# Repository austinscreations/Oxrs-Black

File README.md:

# Oxrs-Black
a custom rack controller that is based of the rack32 but includes some upgrades and major changes

With the latest update on 2024-08-09
- known part qty missing for the optoisolators - these are needed for KNX function. 

you can leave them off or preorder the part before PCBa from JLC
- https://jlcpcb.com/partdetail/avago_broadcom-ACPL_M61L500E/C44908

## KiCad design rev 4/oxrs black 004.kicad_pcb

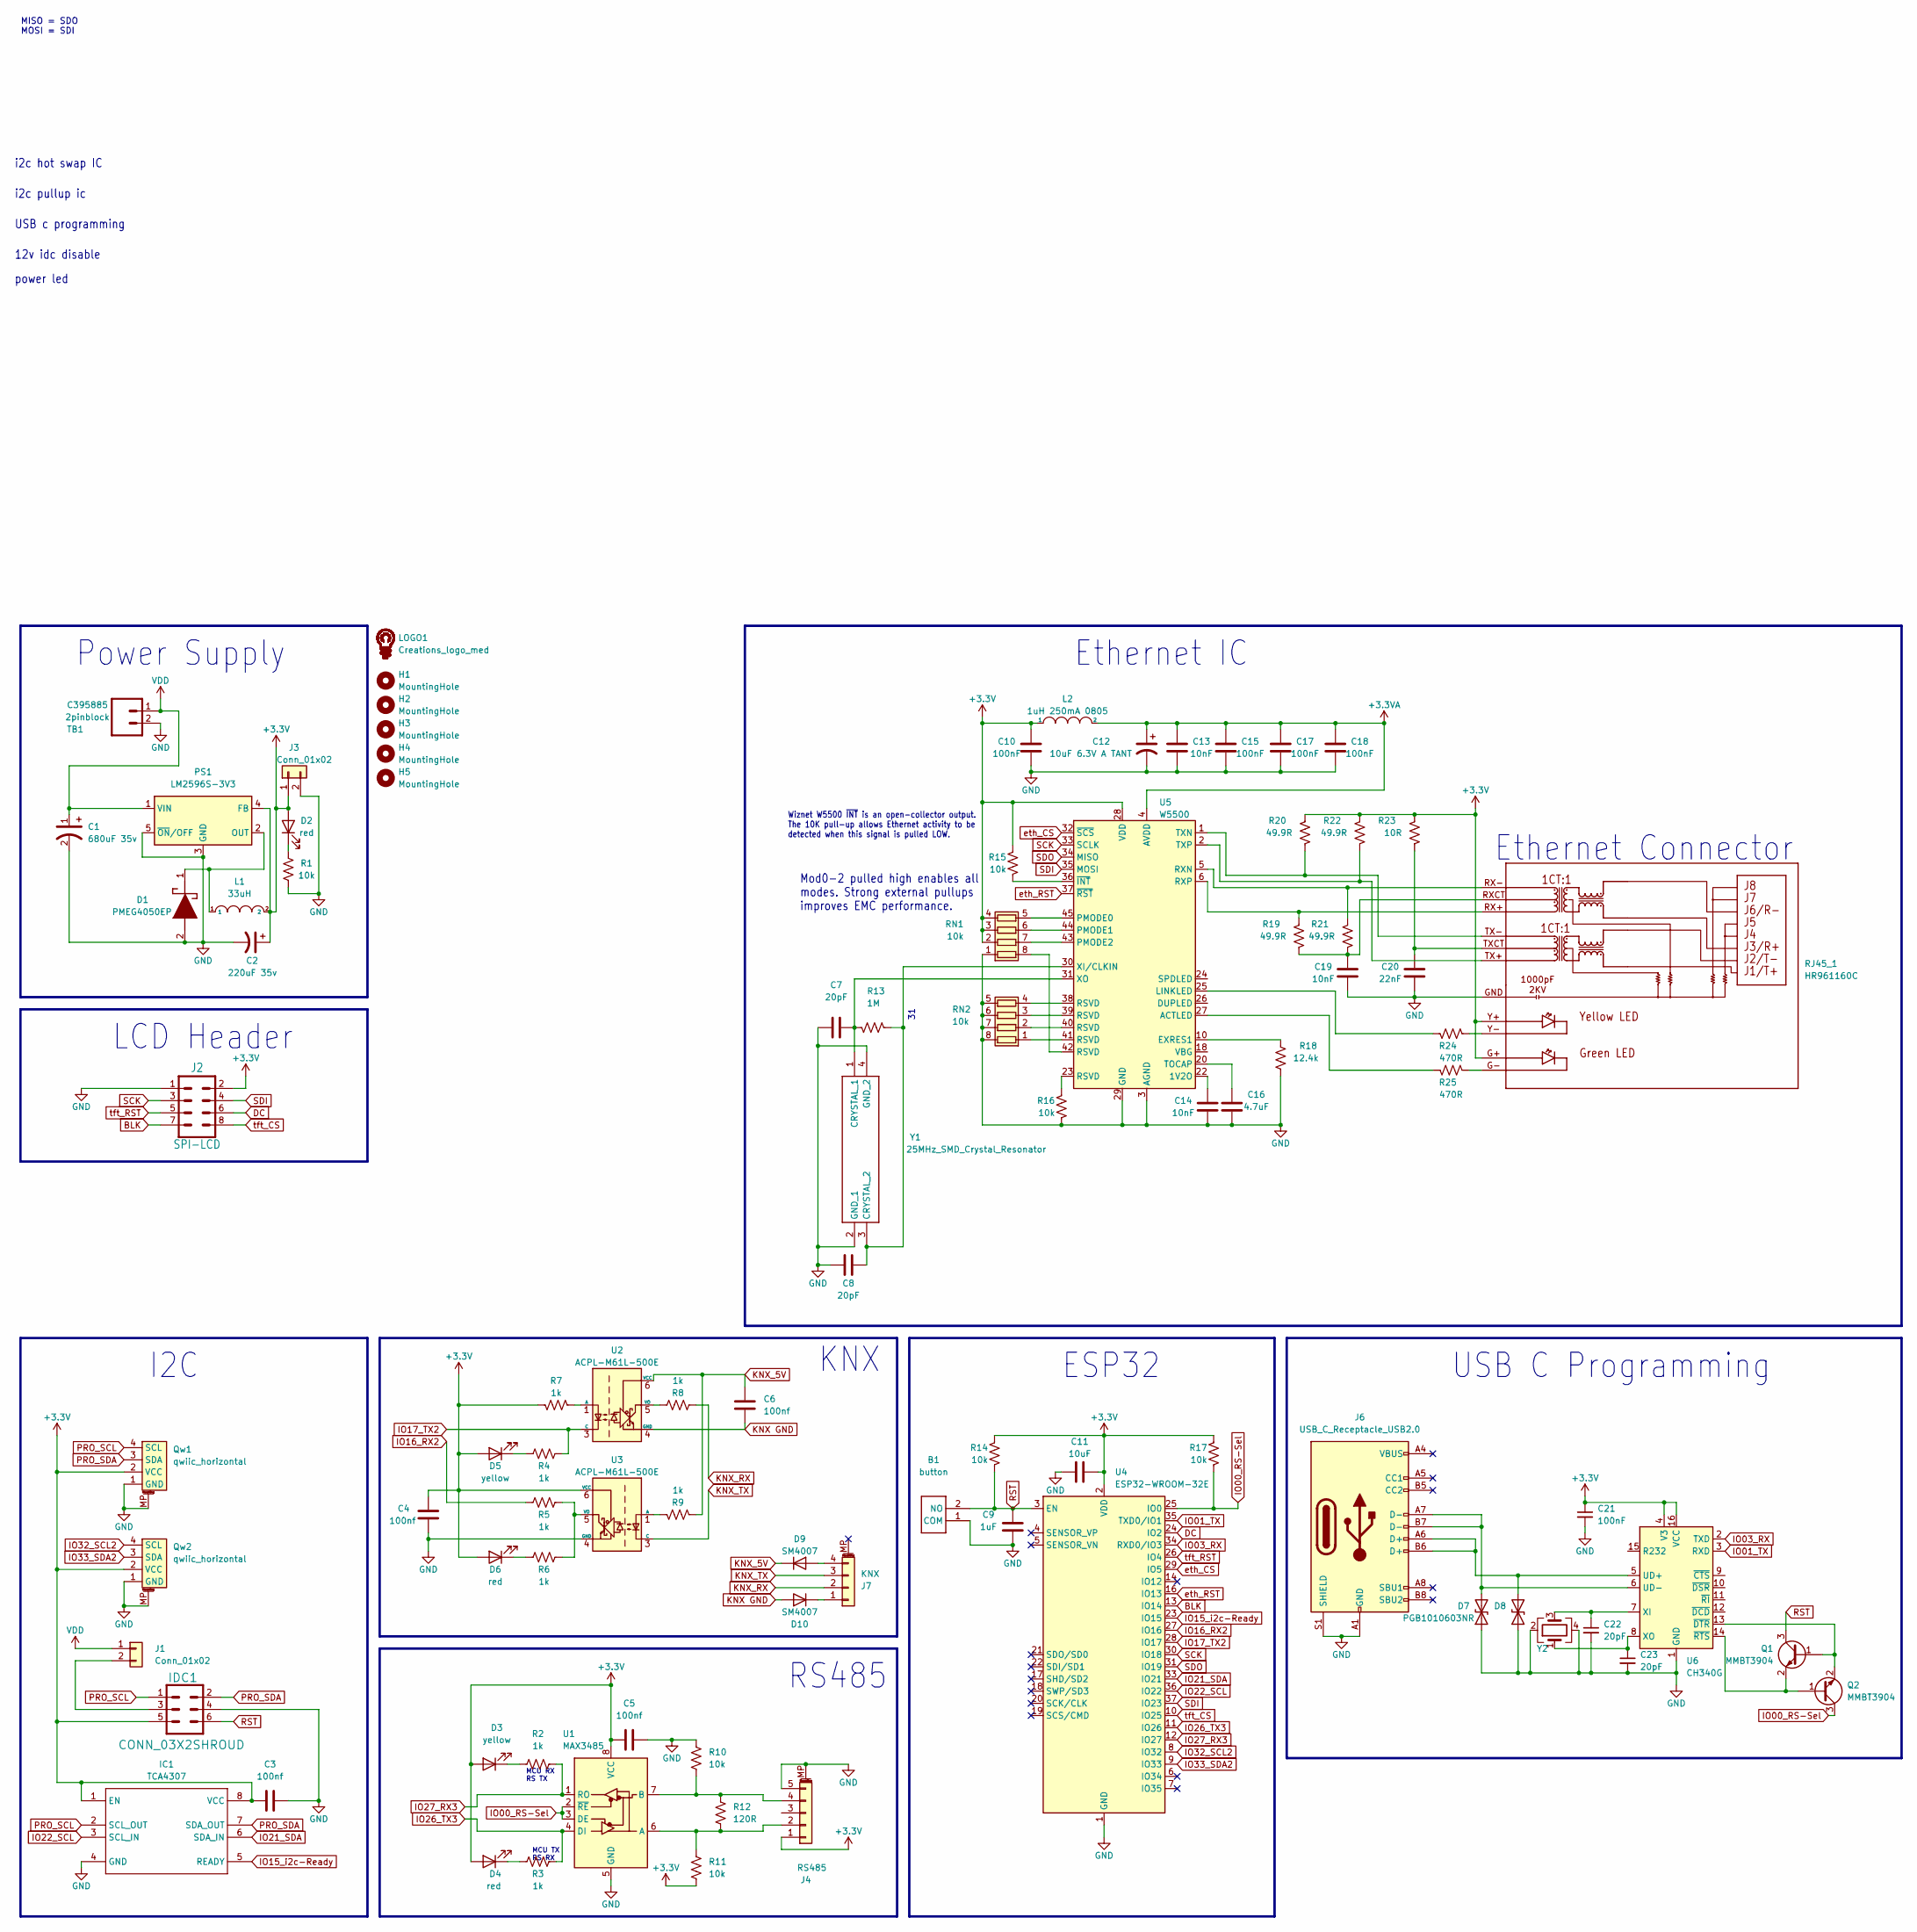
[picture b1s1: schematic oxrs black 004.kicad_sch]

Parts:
B1: button; LCSC C410373
C1: 680uF 35v; large capacitor 12.5d 13.5h; LCSC C98216
C2: 220uF 35v; CP_Elec_8x6.2; LCSC C5162357
C3, C4, C5, C6: 100nf; C_0603_1608Metric; LCSC C14663
C7, C8, C22, C23: 20pF; C_0603_1608Metric; LCSC C1648
C9: 1uF; C_0603_1608Metric; LCSC C15849
C10, C15, C17, C18, C21: 100nF; C_0603_1608Metric; LCSC C14663
C11: 10uF; C_0603_1608Metric; LCSC C19702
C12: 10uF 6.3V A TANT; CP_EIA-3216-18_Kemet-A; LCSC C127946
C13, C14, C19: 10nF; C_0603_1608Metric; LCSC C57112
C16: 4.7uF; C_0603_1608Metric; LCSC C19666
C20: 22nF; C_0603_1608Metric; LCSC C21122
D1: PMEG4050EP; PMEG3050EP; LCSC C96235
D2, D4, D6: red; LED_0603_1608Metric; LCSC C2286
D3, D5: yellow; LED_0603_1608Metric; LCSC C72038
D7, D8: PGB1010603NR; D_0603_1608Metric; LCSC C10677
D9, D10: SM4007; D_SOD-123F; LCSC C64898
H1, H2, H3, H4, H5: MountingHole; MountingHole_3.2mm_M3
IC1: TCA4307; VSSOP-8_3.0x3.0mm_P0.65mm; LCSC C880333
IDC1: CONN_03X2SHROUD; IDC-Header_2x03_P2.54mm_Vertical; LCSC C601936
J1, J3: Conn_01x02; PinHeader_1x02_P2.54mm_Vertical; LCSC C492401
J2: SPI-LCD; IDC-Header_2x04_P2.54mm_Vertical; LCSC C601937
J4: RS485; 5 pin jst 1.25 vertical; LCSC C225107
J6: USB_C_Receptacle_USB2.0; USB_C_Receptacle_HRO_TYPE-C-31-M-12; LCSC C2765186
J7: KNX; 4 pin jst 1.25 vertical; LCSC C225106
L1: 33uH; 12x12x8 inductor; LCSC C9400
L2: 1uH 250mA 0805; L_0805_2012Metric; LCSC C98325
LOGO1: Creations_logo_med; Creations logo med
PS1: LM2596S-3V3; LM2596S; LCSC C347420
Q1, Q2: MMBT3904; SOT-23; LCSC C20526
Qw1, Qw2: qwiic_horizontal; qwiic vertical; part # C145961; LCSC C145956
R1, R10, R11, R14, R15, R16, R17: 10k; R_0603_1608Metric; LCSC C25804
R2, R3, R4, R5, R6, R7, R8, R9: 1k; R_0603_1608Metric; LCSC C21190
R12: 120R; R_0603_1608Metric; LCSC C22787
R13: 1M; R_0603_1608Metric; LCSC C22935
R18: 12.4k; R_0603_1608Metric; LCSC C310267
R19, R20, R21, R22: 49.9R; R_0603_1608Metric; LCSC C23185
R23: 10R; R_0603_1608Metric; LCSC C22859
R24, R25: 470R; R_0603_1608Metric; LCSC C23179
RJ45_1: HR961160C; LCSC C55683
RN1, RN2: 10k; R_Array_Convex_4x0603; LCSC C29718
TB1: 2pinblock; LCSC C395885
U1: MAX3485; SOP-8_3.9x4.9mm_P1.27mm; part # C9943; LCSC C668204
U2, U3: ACPL-M61L-500E; SO-5_4.4x3.6mm_P1.27mm; LCSC C44908
U4: ESP32-WROOM-32E; ESP32-WROOM-32; LCSC C3013935
U5: W5500; LQFP-48_7x7mm_P0.5mm; LCSC C32843
U6: CH340G; SOIC-16_3.9x9.9mm_P1.27mm; LCSC C14267
Y1: 25MHz_SMD_Crystal_Resonator; LCSC C258949
Y2: Crystal_GND23; Crystal_SMD_3225-4Pin_3.2x2.5mm; LCSC C9002

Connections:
+3.3VA: C12.1, C13.2, C15.2, C17.2, C18.2, L2.2, U5.4 (AVDD), U5.8 (AVDD), U5.11 (AVDD), U5.15 (AVDD), U5.17 (AVDD), U5.21 (AVDD)
+3V3: C2.1, C3.2, C4.1, C5.2, C10.2, C11.2, C21.1, D2.2 (A), D3.2 (A), D4.2 (A), D5.2 (A), D6.2 (A), IC1.1 (EN), IC1.8 (VCC), IDC1.5, J2.2, J3.1, J4.1, L1.2, L2.1, PS1.4 (FB), Qw1.2 (VCC), Qw2.2 (VCC), R7.1, R11.1, R14.2, R15.2, R17.2, R20.2, R22.2, R23.2, RJ45_1.G+, RJ45_1.Y+, RN1.2 (R2.1), RN1.3 (R3.1), RN1.4 (R4.1), U1.8 (VCC), U3.6 (VCC), U4.2 (VDD), U5.28 (VDD), U6.4 (V3), U6.16 (VCC)
BLK: J2.7, U4.13 (IO14)
DC: J2.6, U4.24 (IO2)
GND: B1.1 (COM), C1.2, C2.2, C3.1, C4.2, C5.1, C7.1, C8.1, C9.1, C10.1, C11.1, C12.2, C13.1, C14.1, C15.1, C16.1, C17.1, C18.1, C19.1, C20.1, C21.2, C22.2, C23.2, D1.2 (A), D7.1 (A1), D8.1 (A1), IC1.4 (GND), IDC1.4, J2.1, J3.2, J4.5, J4.MP (MountPin), J6.A1 (GND), J6.A12 (GND), J6.B1 (GND), J6.B12 (GND), J6.S1 (SHIELD), PS1.3 (GND), PS1.5 (~ON/OFF), Qw1.1 (GND), Qw1.MP, Qw2.1 (GND), Qw2.MP, R1.2, R10.2, R16.1, R18.1, RJ45_1.GND (GNDF), RN1.1 (R1.1), RN2.5 (R4.2), RN2.6 (R3.2), RN2.7 (R2.2), RN2.8 (R1.2), TB1.2, U1.5 (GND), U3.4 (GND), U4.1 (GND), U4.15 (GND), U4.38 (GND), U4.39 (GND), U5.3 (AGND), U5.9 (AGND), U5.14 (AGND), U5.16 (AGND), U5.19 (AGND), U5.29 (GND), U5.48 (AGND), U6.1 (GND), Y1.2 (GND_1), Y1.4 (GND_2), Y2.2, Y2.4
IO00_RS-Sel: Q2.3 (C), R17.1, U1.2 (~RE), U1.3 (DE), U4.25 (IO0)
IO01_TX: U4.35 (TXD0/IO1), U6.3 (RXD)
IO03_RX: U4.34 (RXD0/IO3), U6.2 (TXD)
IO15_i2c-Ready: IC1.5 (READY), U4.23 (IO15)
IO16_RX2: R5.1, U4.27 (IO16)
IO17_TX2: R4.2, U2.3 (C), U4.28 (IO17)
IO21_SDA: IC1.6 (SDA_IN), U4.33 (IO21)
IO22_SCL: IC1.3 (SCL_IN), U4.36 (IO22)
IO26_TX3: R3.2, U1.4 (DI), U4.11 (IO26)
IO27_RX3: R2.2, U1.1 (RO), U4.12 (IO27)
IO32_SCL2: Qw2.4 (SCL), U4.8 (IO32)
IO33_SDA2: Qw2.3 (SDA), U4.9 (IO33)
KNX GND: C6.2, D10.2 (A), U2.4 (GND)
KNX_5V: C6.1, D9.1 (K), R9.2, U2.6 (VCC)
KNX_RX: J7.2, R8.1
KNX_TX: J7.3, U3.3 (C)
unnamed: C19.2, R19.1, R21.1, RJ45_1.RXCT
unnamed: C20.2, R23.1, RJ45_1.TXCT
unnamed: D1.1 (K), L1.1, PS1.2 (OUT)
unnamed: D2.1 (K), R1.1
unnamed: D3.1 (K), R2.1
unnamed: D4.1 (K), R3.1
unnamed: D5.1 (K), R4.1
unnamed: D6.1 (K), R6.1
unnamed: D7.2 (A2), J6.A7 (D-), J6.B7 (D-), U6.6 (UD-)
unnamed: D8.2 (A2), J6.A6 (D+), J6.B6 (D+), U6.5 (UD+)
unnamed: D9.2 (A), J7.4
unnamed: D10.1 (K), J7.1
unnamed: IDC1.3, J1.2
unnamed: J4.2, R11.2, R12.1, U1.6 (A)
unnamed: J4.4, R10.1, R12.2, U1.7 (B)
unnamed: Q1.1 (B), Q2.2 (E), U6.13 (~DTR)
unnamed: Q1.2 (E), Q2.1 (B), U6.14 (~RTS)
unnamed: R16.2, U5.23 (RSVD)
unnamed: R24.1, RJ45_1.Y-
unnamed: R25.1, RJ45_1.G-
unnamed: RN1.8 (R1.2), U5.42 (RSVD)
unnamed: RN1.7 (R2.2), U5.43 (PMODE2)
unnamed: RN1.6 (R3.2), U5.44 (PMODE1)
unnamed: RN1.5 (R4.2), U5.45 (PMODE0)
unnamed: RN2.1 (R1.1), U5.41 (RSVD)
unnamed: RN2.2 (R2.1), U5.40 (RSVD)
unnamed: RN2.3 (R3.1), U5.39 (RSVD)
unnamed: RN2.4 (R4.1), U5.38 (RSVD)
unnamed: R7.2, U2.1 (A)
unnamed: R8.2, U2.5 (VO)
unnamed: R9.1, U3.1 (A)
unnamed: R5.2, R6.2, U3.5 (VO)
unnamed: C14.2, U5.22 (1V2O)
unnamed: R25.2, U5.27 (ACTLED)
unnamed: R18.2, U5.10 (EXRES1)
unnamed: R24.2, U5.25 (LINKLED)
unnamed: R21.2, RJ45_1.RX-, U5.5 (RXN)
unnamed: R19.2, RJ45_1.RX+, U5.6 (RXP)
unnamed: C16.2, U5.20 (TOCAP)
unnamed: R20.1, RJ45_1.TX-, U5.1 (TXN)
unnamed: R22.1, RJ45_1.TX+, U5.2 (TXP)
unnamed: C8.2, R13.2, U5.30 (XI/CLKIN), Y1.3 (CRYSTAL_2)
unnamed: C7.2, R13.1, U5.31 (XO), Y1.1 (CRYSTAL_1)
unnamed: R15.1, U5.36 (~INT)
unnamed: C22.1, U6.7 (XI), Y2.3
unnamed: C23.1, U6.8 (XO), Y2.1
PRO_SCL: IC1.2 (SCL_OUT), IDC1.1, Qw1.4 (SCL)
PRO_SDA: IC1.7 (SDA_OUT), IDC1.2, Qw1.3 (SDA)
RST: B1.2 (NO), C9.2, IDC1.6, Q1.3 (C), R14.1, U4.3 (EN)
SCK: J2.3, U4.30 (IO18), U5.33 (SCLK)
SDI: J2.4, U4.37 (IO23), U5.35 (MOSI)
SDO: U4.31 (IO19), U5.34 (MISO)
VDD: C1.1, J1.1, PS1.1 (VIN), TB1.1
eth_CS: U4.29 (IO5), U5.32 (~SCS)
eth_RST: U4.16 (IO13), U5.37 (~RST)
tft_CS: J2.8, U4.10 (IO25)
tft_RST: J2.5, U4.26 (IO4)

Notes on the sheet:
I2C
Power Supply
power led
ESP32
Mod0-2 pulled high enables all modes. Strong external pullups improves EMC performance.
LCD Header
KNX
MISO = SDO MOSI = SDI
i2c hot swap IC
i2c pullup ic
Ethernet Connector
USB C Programming
MCU RX RS TX
Ethernet IC
12v idc disable
RS485
MCU TX RS RX
USB c programming
Wiznet W5500 ~{INT} is an open-collector output. The 10K pull-up allows Ethernet activity to be detected when this signal is pulled LOW.

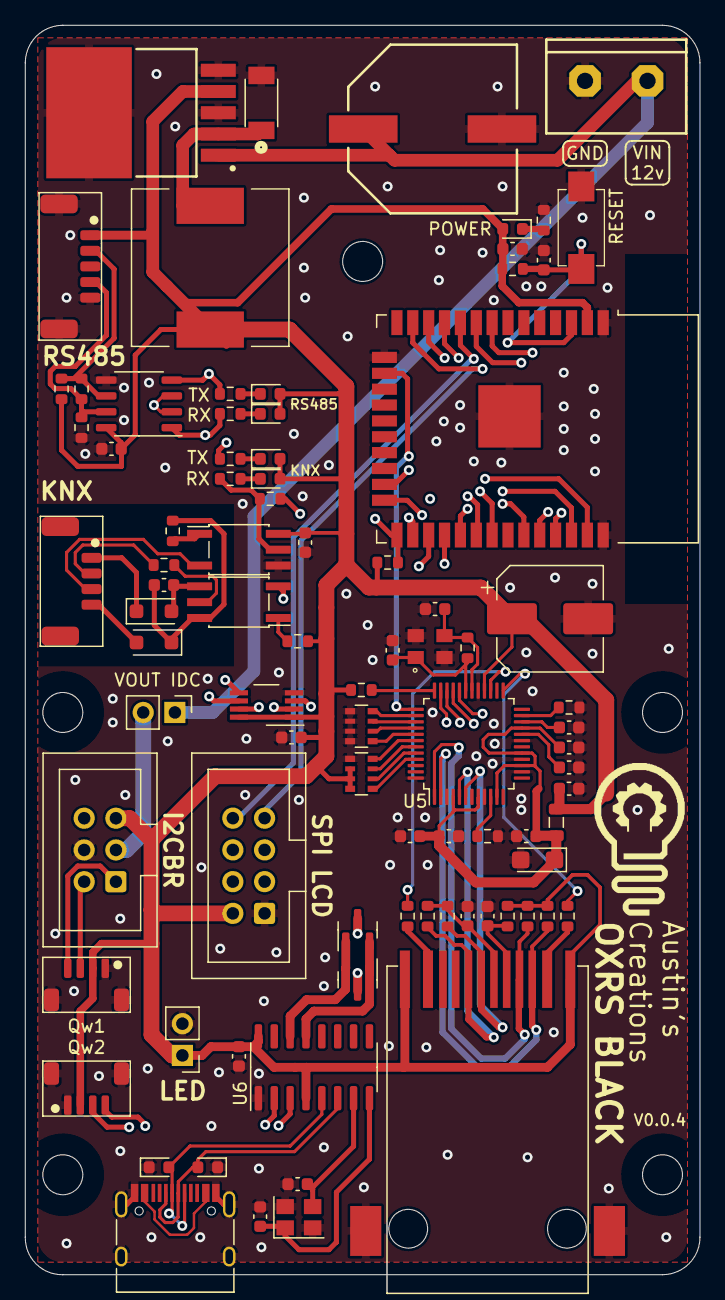
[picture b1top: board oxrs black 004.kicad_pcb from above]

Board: 4 copper layers, 54.0 x 100.0 mm, 92 parts (0 on the bottom side), 78 nets.

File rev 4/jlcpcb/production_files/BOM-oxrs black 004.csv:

Comment,Designator,Footprint,LCSC
PGB1010603NR,"D7,D8",D_0603_1608Metric,C10677
10uF 6.3V A TANT,C12,CP_EIA-3216-18_Kemet-A,C127946
CH340G,U6,SOIC-16_3.9x9.9mm_P1.27mm,C14267
qwiic_horizontal,"Qw1,Qw2",qwiic vertical,C145956
100nF,"C10,C15,C17,C18,C21,C3,C4,C5,C6",C_0603_1608Metric,C14663
1uF,C9,C_0603_1608Metric,C15849
20pF,"C22,C23,C7,C8",C_0603_1608Metric,C1648
4.7uF,C16,C_0603_1608Metric,C19666
10uF,C11,C_0603_1608Metric,C19702
MMBT3904,"Q1,Q2",SOT-23,C20526
22nF,C20,C_0603_1608Metric,C21122
1k,"R2,R3,R4,R5,R6,R7,R8,R9",R_0603_1608Metric,C21190
KNX,J7,4 pin jst 1.25 vertical,C225106
RS485,J4,5 pin jst 1.25 vertical,C225107
120R,R12,R_0603_1608Metric,C22787
10R,R23,R_0603_1608Metric,C22859
red,"D2,D4,D6",LED_0603_1608Metric,C2286
1M,R13,R_0603_1608Metric,C22935
470R,"R24,R25",R_0603_1608Metric,C23179
49.9R,"R19,R20,R21,R22",R_0603_1608Metric,C23185
10k,"R1,R10,R11,R14,R15,R16,R17",R_0603_1608Metric,C25804
25MHz_SMD_Crystal_Resonator,Y1,25MHz_SMD_Crystal_Resonator,C258949
USB_C_Receptacle_USB2.0,J6,USB_C_Receptacle_HRO_TYPE-C-31-M-12,C2765186
10k,"RN1,RN2",R_Array_Convex_4x0603,C29718
ESP32-WROOM-32E,U4,ESP32-WROOM-32,C3013935
12.4k,R18,R_0603_1608Metric,C310267
W5500,U5,LQFP-48_7x7mm_P0.5mm,C32843
LM2596S-3V3,PS1,LM2596S,C347420
2pinblock,TB1,2pinblock,C395885
button,B1,button,C410373
ACPL-M61L-500E,"U2,U3",SO-5_4.4x3.6mm_P1.27mm,C44908
Conn_01x02,"J1,J3",PinHeader_1x02_P2.54mm_Vertical,C492401
220uF 35v,C2,CP_Elec_8x6.2,C5162357
HR961160C,RJ45_1,HR961160C,C55683
10nF,"C13,C14,C19",C_0603_1608Metric,C57112
CONN_03X2SHROUD,IDC1,IDC-Header_2x03_P2.54mm_Vertical,C601936
SPI-LCD,J2,IDC-Header_2x04_P2.54mm_Vertical,C601937
SM4007,"D10,D9",D_SOD-123F,C64898
MAX3485,U1,SOP-8_3.9x4.9mm_P1.27mm,C668204
yellow,"D3,D5",LED_0603_1608Metric,C72038
TCA4307,IC1,VSSOP-8_3.0x3.0mm_P0.65mm,C880333
Crystal_GND23,Y2,Crystal_SMD_3225-4Pin_3.2x2.5mm,C9002
33uH,L1,12x12x8 inductor,C9400
PMEG4050EP,D1,PMEG3050EP,C96235
680uF 35v,C1,large capacitor 12.5d 13.5h,C98216
1uH 250mA 0805,L2,L_0805_2012Metric,C98325

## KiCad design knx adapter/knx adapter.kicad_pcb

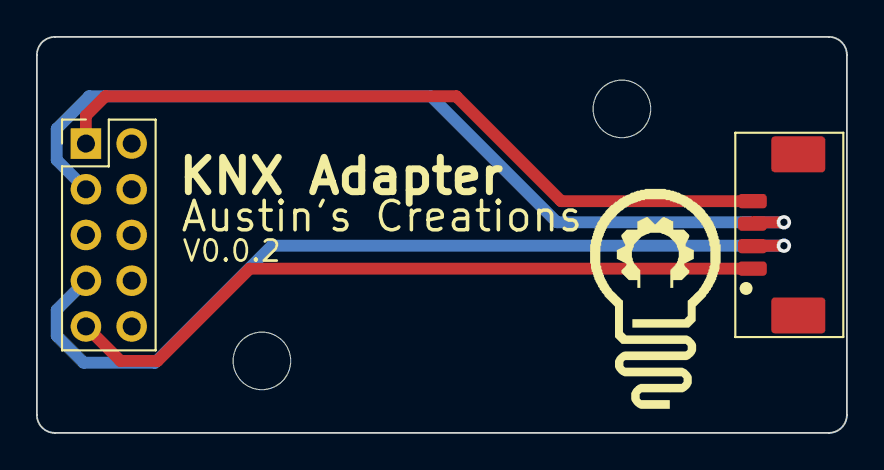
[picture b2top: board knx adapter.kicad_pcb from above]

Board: 2 copper layers, 45.0 x 22.0 mm, 5 parts (0 on the bottom side), 4 nets.

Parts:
H1, H2: MountingHole; MountingHole_3.2mm_M3
J1: Conn_02x05_Odd_Even; PinHeader_2x05_P2.54mm_Vertical
J2: KNX; 4 pin jst 1.25 horizontal
LOGO1: Creations_logo_med; Creations logo med

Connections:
KNX GND: J1.9, J2.1
KNX_5V: J1.1, J2.4
KNX_RX: J1.7, J2.2
KNX_TX: J1.3, J2.3

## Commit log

2024-08-09 update adapter to rev 002
2024-08-09 newest and tested version of oxrs black
2024-08-09 update the renders to match changes
2024-08-15 incorrect part number for qwiic was used
